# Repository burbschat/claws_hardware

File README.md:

# Simple SiPM/plastic scintillator based beam loss monitors
## Introduction
This repository contains the hardware design for a kind of SiPM/plastic
scintillator based beam loss monitor.
The design is based on and borrows the name (*CLAWS*) from an earlier design
employed during commissioning of the SuperKEKB collider.
A related thesis can be found [here](https://mediatum.ub.tum.de/1624845).
CLAWS was supposed to be a abbreviation for some longer name but it surely
wasn't a very elegant one, neither can I seem to remember it. Anyhow, as a
short name is quite practical, we kept on calling the system *CLAWS*.

The sensors later have been re-purposed to detect beam loss and trigger a beam
abort if there is too much of it. This application does not require very
precise sensors. Further, opposed to the original design, now a larger dynamic
range was desirable. To also allow for measurement of beam backgrounds
which occur for longer than a few microseconds, DC coupled analog electronics
are required.
The design published here was created to implement the required changes
outlined above and create a system better suited to the current application at
the SuperKEKB collider.

## Disclaimer
The circuits here have been designed by an at the time undergrad student (me)
who had no real experience in electronics or electronics CAD. I am sure there
are many aspects that I would do differently now, be it related to the circuit
itself or how it is described in KiCad.
I am however of course open for suggestions to improve the design (although I
cannot guarantee I will find the time to implement them myself).

## Overview
There are two parts to the detector system: The detectors, which are to be
placed where the beam background is expected to occur and the receiver board,
which should be placed near the digitizer, which is usually positioned outside
the radiation controlled area of the accelerator complex.

The following is an illustration of the use case at SuperKEKB (use for beam
abort), also illustrating the detector structure.
We employ a special trigger to reject short background spikes. The analog
signal however can be used in any other conceivable way depending on the exact
application.

### Detector Board
The detector (sometimes also referred to as the sensor) is based on a plastic
scintillator (BC-408 or similar material), light from which is detected using a
Hamamatsu SiPM (or MPPC). The SiPM is located in a small dimple in the bottom
of the scintillator. The scintillator is wrapped in an appropriately sized
reflective film (M3 DF2000MA or similar) to make sure as much as possible light
reaches the SiPM. This is the same as what was used with the earlier versions
of CLAWS and can be traced back to what is described in [this paper](https://arxiv.org/abs/1512.05900).
The wrapped scintillator is fixed to the PCB using black aluminium tape, which
also serves to shut out any light from the environment, which would overwhelm
(and potentially damage) the SiPM.

The signal obtained from the SiPM is turned into a differential signal using
the LMH6553 fully differential amplifier. The gain of this amplifier may be set
by choosing appropriate resistor values in the feedback loops of the circuit.
This amplifier then drives a differential pair in an ordinary Ethernet cable.
However, generally only CAT6A or CAT7 cables are used, as they usually provide
superior shielding, which even though a differential pair is used, appeared to
significantly lower the noise introduced by the cable.

The required voltages to drive the amplifier circuit as well as the SiPM bias
voltage are obtained from the same Ethernet cable. The amplifier here is
configured with a single 10V power supply. The voltage in the cable should be
slightly above 10V, as it is regulated by a LDO regulator on the detector
board.
10V is the maximum supply voltage supported by the LMH6553 and is chosen to
maximize the dynamic range at the amplifier output (which depends on the supply
voltage).

One twisted pair in the cable remains unused for now.

### Receiver Board
The differential signal provided by the detector board is received and properly
terminated by the receiver board. It contains a circuit using the same LMH6553
fully differential amplifier, which provides further amplification of the
received signal, as well as the option to convert it to a single ended signal.
Both inverted and non-inverted signals are supported. The not used side must be
terminated using a 50Ohm resistor (which can however also be mounted directly
on the board while leaving the corresponding output connector unpopulated).
There also is the option to further use both outputs at the same time to obtain
a differential signal.

The receiver amplifier circuit is, opposed to the one on the detector board,
arranged in a symmetric configuration. This is done to avoid a large DC bias at
the output, which poses no problem for in case of the detector board, as it is
removed by the receiver amplification circuit. The symmetric configuration
necessitates +5V and -5V supplies (for both of which there are LDO regulators
on the board).

Presumably due some unavoidable variations in the used components (resistance
values etc.), the circuit is never perfectly symmetric and thus a small DC bias
remains. The same bias appears at both outputs (inverted and non-inverted).
To compensate this, the common mode output voltage control pin of the LMH6553
is used, which is accessible through a potentiometer on the board.
As the bias is present at both outputs, one can only ever tune the circuit to
have one of them centered perfectly around zero. This however should pose no
significant problem, as in most use cases one probably only uses one of the two
outputs, or uses both to get a differential signal, for which a small DC bias
does not matter.

The Receiver board further also distributes the voltages required by the
detector boards. These voltages as well as those needed by the receiver board
itself are supplied externally through connectors on the side of the board.
There further is the option to daisy-chain multiple receiver boards and share
the supply voltages between them. Which voltage should be connected to what is
to some degree configurable using a set of jumper pins. As regulators are used
for all but the SiPM bias voltage, the low voltages provided can be chosen
rather freely, as long as they fall within the ranges supported input of the
LDO regulators. However, testing showed that if they are on the high side, the
LDOs get rather hot. Whether this is still within the supported temperature
range was not (yet) verified.

There is also an option to use the positive voltage (before the LDO) for the
receiver board amplifier as the positive voltage for the detector board
amplifier. This turned out to be the most convenient configuration as it allows 
the setup to be powered off a +/-12V double rail supply (next to a supply for
the SiPM bias voltage).

To share voltages between receiver boards, a 10-pin ribbon cable is used. The
boards may be arranged in a stacked configuration, in case of which the
connector on the bottom must be installed and used, or a flat configuration
with a single long ribbon cable with multiple connectors.

A example for the stacked configuration is shown below. There is theoretically
also the option to add further boards of the same form factor which for example
may contain a high voltage power supply to provide the SiPM bias voltage, or
DC/DC converters to provide the other supply voltages. A mockup is shown in the
figure below.

### SiPM Bias Voltage Supply
To avoid having to prepare a adjustable power supply supporting up to ~60V for
every setup, it was attempted to design a simple circuit based on the LT3571
75V DC/DC Converter for APD Bias.
The design appears to function alright, but does not provide a very flat voltage.
This to some extend is reflected in the signal form the SiPM. However, for the
application at SuperKEKB, the signal does not have to be very precise and the
introduced noise can be tolerated.

The board also does indeed emit some EMI, so care must be taken on where to
position it. There likely are possibilities to improve this design. I am open
for suggestions.

The board can be run off the same +12V as used as an input to the receiver
board. There is the option to use a DAC in combination with a microcontroller
to set the voltages and possibly read them back. I did not yet get around to
prepare a proper firmware for that. One can also simply adjust the voltage 
using a potentiometer.

There are four channels on one board, just because four of them appeared to
fit. One can just not populate the unused ones, if less than four are required.
The board does not support the same interconnect headers as the receiver boards.
This is because it mainly was designed to see if the circuit does work/is
usable at all. One could create a new version with only one channel featuring
the interconnect header.

## KiCad
The design is entirely drawn in KiCad. I like to use the newest version. The
files in this repository are for version 9.

## Libraries
There is are custom symbol and footprint library containing all the parts not
present in the standard KiCad libraries. The provided 3D models are managed
with git LFS.

## Simulation
Some of the symbols reference SPICE models in the `${KIPRJMOD}/../lib/spice_models/` directory.
Those are not present in this repository as I am probably not permitted to distribute them.
If simulation is required, please acquire the models directly from the manufacturers.

## KiBot
KiBot can be used to automate creation of gerber files, export circuit diagrams
and assembly documents or similar. The included configs are those which I used
when producing the boards at use for the SuperKEKB abort system. Adjust to taste.

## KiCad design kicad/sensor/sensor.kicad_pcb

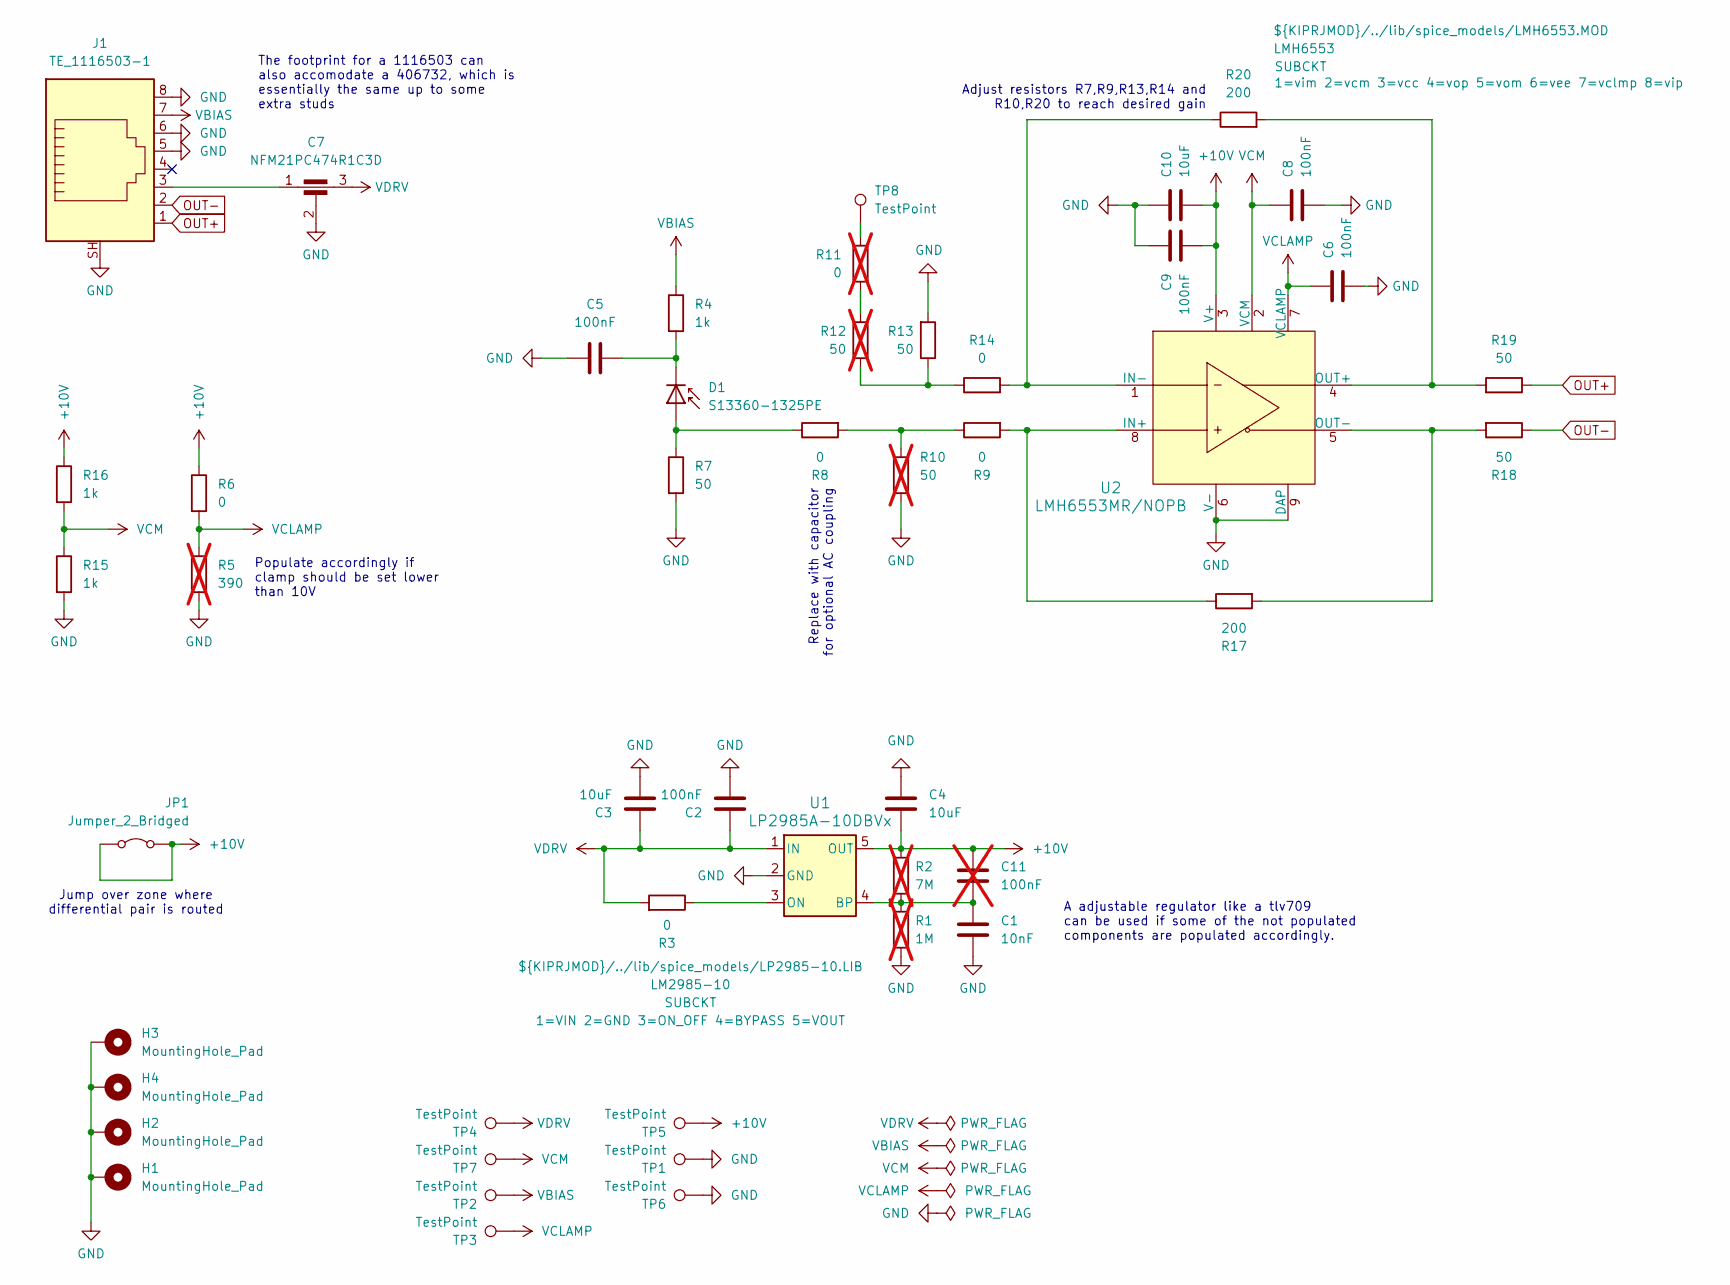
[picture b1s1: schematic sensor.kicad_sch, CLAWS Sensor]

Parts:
C1: 10nF; C_0603_1608Metric; Part Number GRM188R72A103KA01D
C2, C5, C6, C8, C9: 100nF; C_0603_1608Metric; Part Number GRM188R72A104KA35D
C3, C4, C10: 10uF; C_0603_1608Metric; Part Number GRM188R61E106KA73D
C7: NFM21PC474R1C3D; NFM21PC225B0J3D_MUR; Part Number NFM21PC474R1C3D
C11: 100nF; C_0603_1608Metric; Part Number GRM188R72A104KA35D; not fitted
D1: S13360-1325PE; Hamamatsu_Sxxx60-13xxXX_hand_solder; Part Number S13360-1325PE
H1, H2, H3, H4: MountingHole_Pad; MountingHole_3.2mm_M3_ISO7380_Pad_TopBottom
J1: TE_1116503-1; TE_1116503; Part Number TE_1116503-1
JP1: Jumper_2_Bridged; R_2512_6332Metric; Part Number ERJ-U1T0R00U
R1: 1M; R_0603_1608Metric; not fitted
R2: 7M; R_0603_1608Metric; not fitted
R3, R6, R8, R9, R14: 0; R_0603_1608Metric; Part Number ERJ-3GEY0R00V
R4, R15, R16: 1k; R_0603_1608Metric; Part Number ERJ-3EKF1001V
R5: 390; R_0603_1608Metric; not fitted
R7, R13, R18, R19: 50; R_0603_1608Metric; Part Number ERJ-3EKF49R9V
R10, R12: 50; R_0603_1608Metric; Part Number ERJ-3EKF49R9V; not fitted
R11: 0; R_0603_1608Metric; Part Number ERJ-3GEY0R00V; not fitted
R17, R20: 200; R_0603_1608Metric; Part Number ERJ-3GEYJ201V
TP1, TP2, TP3, TP4, TP5, TP6, TP7, TP8: TestPoint; TestPoint_THTPad_D1.5mm_Drill0.7mm
U1: LP2985A-10DBVx; SOT-23-5_DBV_TEX; Part Number LP2985A-10DBVR
U2: LMH6553MR/NOPB; MRA08B; Part Number LMH6553MRE/NOPB

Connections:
+10V: C4.1, C9.1, C10.1, C11.2, JP1.1 (A), JP1.2 (B), R2.1, R6.1, R16.1, TP5.1, U1.5 (OUT), U2.3 (V+)
GND: C1.1, C2.1, C3.1, C4.2, C5.1, C6.1, C7.2, C8.1, C9.2, C10.2, H1.1, H2.1, H3.1, H4.1, J1.5, J1.6, J1.8, J1.SH, R1.2, R5.2, R7.2, R10.2, R13.2, R15.2, TP1.1, TP6.1, U1.2 (GND), U2.6 (V-), U2.9 (DAP)
unnamed: C7.1, J1.3
unnamed: D1.3 (A), R7.1, R8.1
unnamed: C5.2, D1.2 (K), R4.2
unnamed: R8.2, R9.1, R10.1
unnamed: R11.1, TP8.1
unnamed: R11.2, R12.2
unnamed: R12.1, R13.1, R14.1
unnamed: C1.2, C11.1, R1.1, R2.2, U1.4 (BP)
unnamed: R3.1, U1.3 (ON)
unnamed: R9.2, R17.1, U2.8 (IN+)
unnamed: R14.2, R20.1, U2.1 (IN-)
unnamed: R19.2, R20.2, U2.4 (OUT+)
unnamed: R17.2, R18.2, U2.5 (OUT-)
OUT+: J1.1, R19.1
OUT-: J1.2, R18.1
VBIAS: J1.7, R4.1, TP2.1
VCLAMP: C6.2, R5.1, R6.2, TP3.1, U2.7 (VCLAMP)
VCM: C8.2, R15.1, R16.2, TP7.1, U2.2 (VCM)
VDRV: C2.2, C3.2, C7.3, R3.2, TP4.1, U1.1 (IN)

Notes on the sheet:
Adjust resistors R7,R9,R13,R14 and R10,R20 to reach desired gain
Replace with capacitor for optional AC coupling
The footprint for a 1116503 can also accomodate a 406732, which is essentially the same up to some extra studs
A adjustable regulator like a tlv709 can be used if some of the not populated components are populated accordingly.
Populate accordingly if clamp should be set lower than 10V
Jump over zone where differential pair is routed

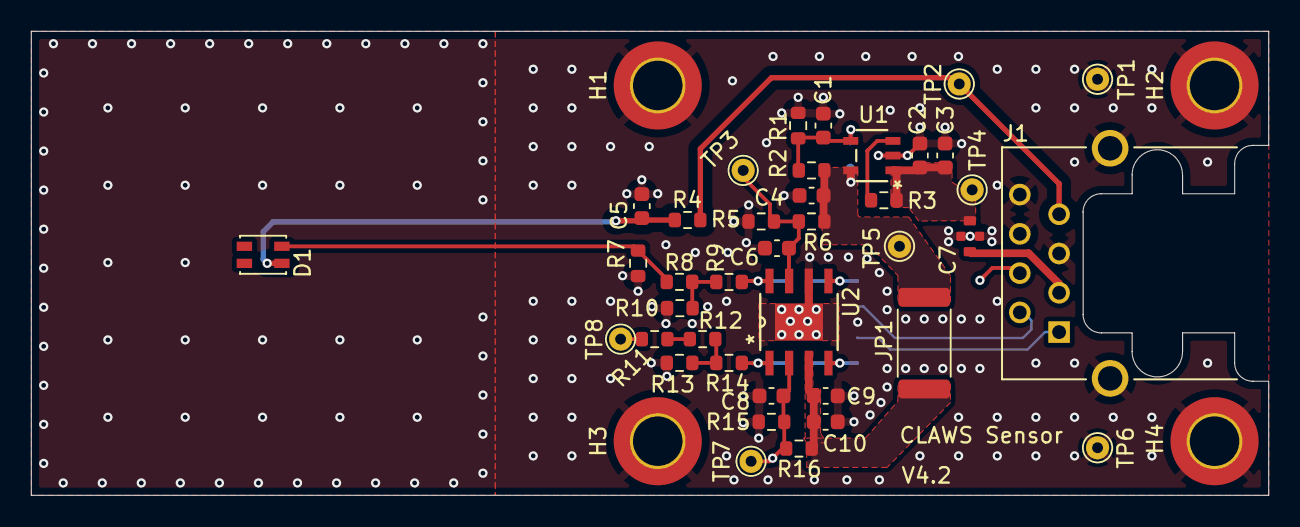
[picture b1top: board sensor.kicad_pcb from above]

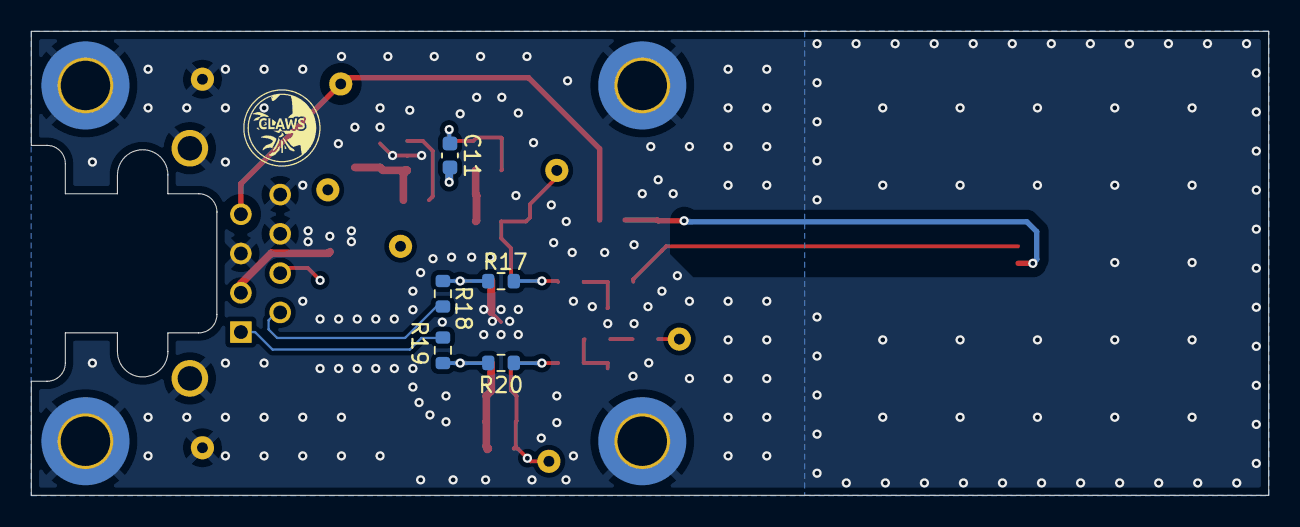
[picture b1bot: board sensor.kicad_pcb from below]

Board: 2 copper layers, 80.0 x 30.0 mm, 48 parts (5 on the bottom side), 21 nets.

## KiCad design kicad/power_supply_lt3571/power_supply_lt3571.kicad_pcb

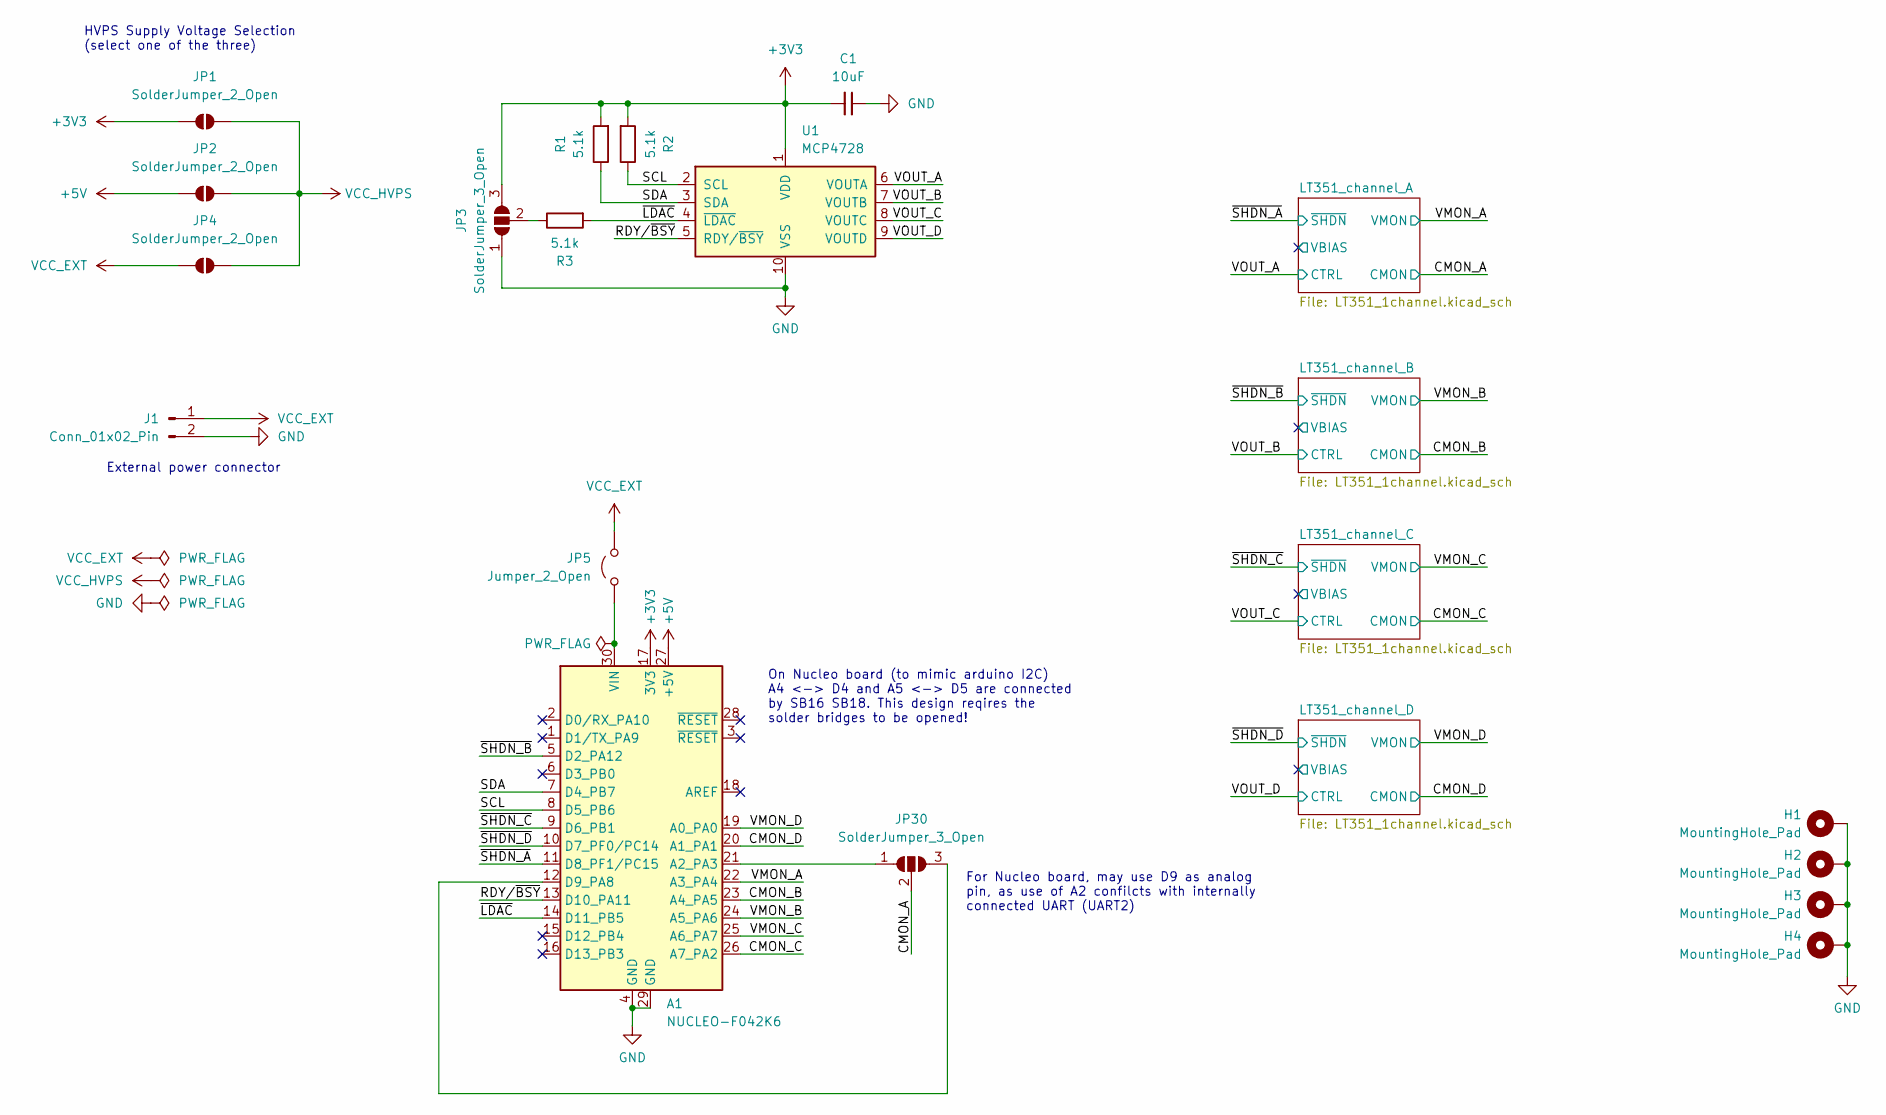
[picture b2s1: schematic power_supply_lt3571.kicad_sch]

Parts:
A1: NUCLEO-F042K6; NUCLEO_NANO_Hybrid
C1: 10uF; C_0603_1608Metric
H1, H2, H3, H4: MountingHole_Pad; MountingHole_3.2mm_M3_Pad_Via
J1: Conn_01x02_Pin; PhoenixContact_MCV_1,5_2-G-3.81_1x02_P3.81mm_Vertical
JP1, JP2, JP4: SolderJumper_2_Open; SolderJumper-2_P1.3mm_Open_TrianglePad1.0x1.5mm
JP3, JP30: SolderJumper_3_Open; SolderJumper-3_P2.0mm_Open_TrianglePad1.0x1.5mm_NumberLabels
JP5: Jumper_2_Open; PinHeader_1x02_P2.54mm_Vertical
R1, R2, R3: 5.1k; R_0603_1608Metric
U1: MCP4728; MSOP-10_3x3mm_P0.5mm

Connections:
+3V3: A1.17 (3V3), C1.2, JP1.1 (A), JP3.3 (B), R1.2, R2.2, U1.1 (VDD)
+5V: A1.27 (+5V), JP2.1 (A)
/CMON_A: JP30.2 (C); also elsewhere on the board
/CMON_B: A1.23 (A4_PA5); also elsewhere on the board
/CMON_C: A1.26 (A7_PA2); also elsewhere on the board
/CMON_D: A1.20 (A1_PA1); also elsewhere on the board
/RDY/~BSY: A1.13 (D10_PA11), U1.5 (RDY/~BSY)
/SCL: A1.8 (D5_PB6), R2.1, U1.2 (SCL)
/SDA: A1.7 (D4_PB7), R1.1, U1.3 (SDA)
/VMON_A: A1.22 (A3_PA4); also elsewhere on the board
/VMON_B: A1.24 (A5_PA6); also elsewhere on the board
/VMON_C: A1.25 (A6_PA7); also elsewhere on the board
/VMON_D: A1.19 (A0_PA0); also elsewhere on the board
/VOUT_A: U1.6 (VOUTA); also elsewhere on the board
/VOUT_B: U1.7 (VOUTB); also elsewhere on the board
/VOUT_C: U1.8 (VOUTC); also elsewhere on the board
/VOUT_D: U1.9 (VOUTD); also elsewhere on the board
/~LDAC: A1.14 (D11_PB5), R3.2, U1.4 (~LDAC)
/~SHDN_A: A1.11 (D8_PF1/PC15); also elsewhere on the board
/~SHDN_B: A1.5 (D2_PA12); also elsewhere on the board
/~SHDN_C: A1.9 (D6_PB1); also elsewhere on the board
/~SHDN_D: A1.10 (D7_PF0/PC14); also elsewhere on the board
GND: A1.4 (GND), A1.29 (GND), C1.1, H1.1, H2.1, H3.1, H4.1, J1.2, JP3.1 (A), U1.10 (VSS); also elsewhere on the board
unnamed: A1.21 (A2_PA3), JP30.1 (A)
unnamed: A1.12 (D9_PA8), JP30.3 (B)
unnamed: A1.30 (VIN), JP5.1 (A)
unnamed: JP3.2 (C), R3.1
VCC_EXT: J1.1, JP4.1 (A), JP5.2 (B)
VCC_HVPS: JP1.2 (B), JP2.2 (B), JP4.2 (B); also elsewhere on the board

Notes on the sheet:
On Nucleo board (to mimic arduino I2C) A4 <-> D4 and A5 <-> D5 are connected by SB16 SB18. This design reqires the solder bridges to be opened!
External power connector
HVPS Supply Voltage Selection (select one of the three)
For Nucleo board, may use D9 as analog pin, as use of A2 confilcts with internally connected UART (UART2)

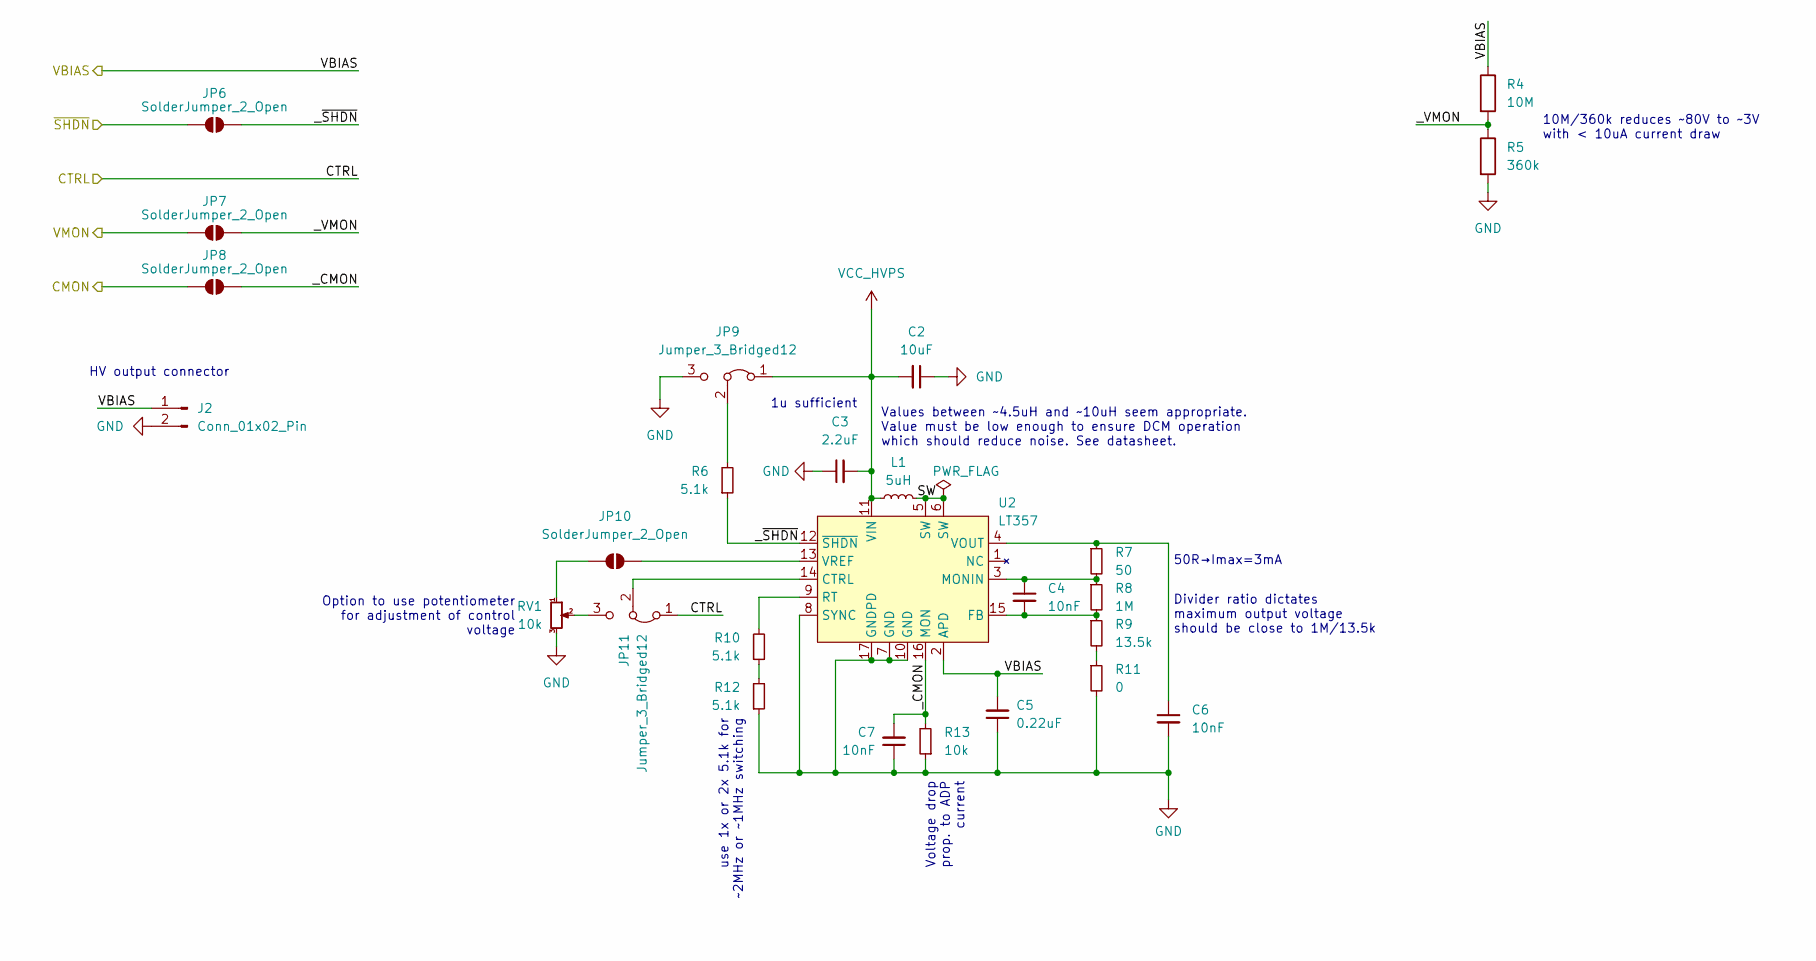
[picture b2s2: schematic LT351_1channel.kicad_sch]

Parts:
C2: 10uF; C_0603_1608Metric
C3: 2.2uF; C_0603_1608Metric
C4, C6, C7: 10nF; C_0603_1608Metric
C5: 0.22uF; C_1206_3216Metric
J2: Conn_01x02_Pin; PhoenixContact_MC_1,5_2-G-3.81_1x02_P3.81mm_Horizontal
JP6, JP7, JP8, JP10: SolderJumper_2_Open; SolderJumper-2_P1.3mm_Open_TrianglePad1.0x1.5mm
JP9, JP11: Jumper_3_Bridged12; PinHeader_1x03_P2.54mm_Vertical
L1: 5uH; L_1210_3225Metric
R4: 10M; R_0603_1608Metric
R5: 360k; R_0603_1608Metric
R6, R10, R12: 5.1k; R_0603_1608Metric
R7: 50; R_0603_1608Metric
R8: 1M; R_0603_1608Metric
R9: 13.5k; R_0603_1608Metric
R11: 0; R_0603_1608Metric
R13: 10k; R_0603_1608Metric
RV1: 10k; Potentiometer_Bourns_3296X_Horizontal
U2: LT357; QFN-16-1EP_3x3mm_P0.5mm_EP1.45x1.45mm_ThermalVias

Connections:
/CMON_A: JP8.1 (A); also elsewhere on the board
/LT351_channel_A/SW: L1.2, U2.5 (SW), U2.6 (SW)
/LT351_channel_A/VBIAS: C5.2, J2.1, R4.1, U2.2 (APD)
/LT351_channel_A/_CMON: C7.2, JP8.2 (B), R13.2, U2.16 (MON)
/LT351_channel_A/_VMON: JP7.2 (B), R4.2, R5.1
/LT351_channel_A/_~SHDN: JP6.2 (B), R6.1, U2.12 (~SHDN)
/VMON_A: JP7.1 (A); also elsewhere on the board
/VOUT_A: JP11.1 (A); also elsewhere on the board
/~SHDN_A: JP6.1 (A); also elsewhere on the board
GND: C2.1, C3.1, C5.1, C6.2, C7.1, J2.2, JP9.3 (B), R5.2, R11.2, R12.1, R13.1, RV1.3, U2.7 (GND), U2.8 (SYNC), U2.10 (GND), U2.17 (GNDPD); also elsewhere on the board
unnamed: JP9.2 (C), R6.2
unnamed: JP10.1 (A), RV1.1
unnamed: JP10.2 (B), U2.13 (VREF)
unnamed: JP11.3 (B), RV1.2
unnamed: JP11.2 (C), U2.14 (CTRL)
unnamed: R10.1, R12.2
unnamed: R9.2, R11.1
unnamed: C4.2, R8.2, R9.1, U2.15 (FB)
unnamed: C4.1, R7.2, R8.1, U2.3 (MONIN)
unnamed: R10.2, U2.9 (RT)
unnamed: C6.1, R7.1, U2.4 (VOUT)
VCC_HVPS: C2.2, C3.2, JP9.1 (A), L1.1, U2.11 (VIN); also elsewhere on the board

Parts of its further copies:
C8, C14, C20: 10uF; C_0603_1608Metric
C9, C15, C21: 2.2uF; C_0603_1608Metric
C10, C12, C13, C16, C18, C19, C22, C24, C25: 10nF; C_0603_1608Metric
C11, C17, C23: 0.22uF; C_1206_3216Metric
J3, J4, J5: Conn_01x02_Pin; PhoenixContact_MC_1,5_2-G-3.81_1x02_P3.81mm_Horizontal
JP12, JP13, JP14, JP16, JP18, JP19, JP20, JP22, JP24, JP25, JP26, JP28: SolderJumper_2_Open; SolderJumper-2_P1.3mm_Open_TrianglePad1.0x1.5mm
JP15, JP17, JP21, JP23, JP27, JP29: Jumper_3_Bridged12; PinHeader_1x03_P2.54mm_Vertical
L2, L3, L4: 5uH; L_1210_3225Metric
R14, R24, R34: 10M; R_0603_1608Metric
R15, R25, R35: 360k; R_0603_1608Metric
R16, R20, R22, R26, R30, R32, R36, R40, R42: 5.1k; R_0603_1608Metric
R17, R27, R37: 50; R_0603_1608Metric
R18, R28, R38: 1M; R_0603_1608Metric
R19, R29, R39: 13.5k; R_0603_1608Metric
R21, R31, R41: 0; R_0603_1608Metric
R23, R33, R43: 10k; R_0603_1608Metric
RV2, RV3, RV4: 10k; Potentiometer_Bourns_3296X_Horizontal
U3, U4, U5: LT357; QFN-16-1EP_3x3mm_P0.5mm_EP1.45x1.45mm_ThermalVias

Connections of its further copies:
/CMON_B: JP14.1 (A); also elsewhere on the board
/CMON_C: JP20.1 (A); also elsewhere on the board
/CMON_D: JP26.1 (A); also elsewhere on the board
/LT351_channel_B/SW: L2.2, U3.5 (SW), U3.6 (SW)
/LT351_channel_B/VBIAS: C11.2, J3.1, R14.1, U3.2 (APD)
/LT351_channel_B/_CMON: C13.2, JP14.2 (B), R23.2, U3.16 (MON)
/LT351_channel_B/_VMON: JP13.2 (B), R14.2, R15.1
/LT351_channel_B/_~SHDN: JP12.2 (B), R16.1, U3.12 (~SHDN)
/LT351_channel_C/SW: L3.2, U4.5 (SW), U4.6 (SW)
/LT351_channel_C/VBIAS: C17.2, J4.1, R24.1, U4.2 (APD)
/LT351_channel_C/_CMON: C19.2, JP20.2 (B), R33.2, U4.16 (MON)
/LT351_channel_C/_VMON: JP19.2 (B), R24.2, R25.1
/LT351_channel_C/_~SHDN: JP18.2 (B), R26.1, U4.12 (~SHDN)
/LT351_channel_D/SW: L4.2, U5.5 (SW), U5.6 (SW)
/LT351_channel_D/VBIAS: C23.2, J5.1, R34.1, U5.2 (APD)
/LT351_channel_D/_CMON: C25.2, JP26.2 (B), R43.2, U5.16 (MON)
/LT351_channel_D/_VMON: JP25.2 (B), R34.2, R35.1
/LT351_channel_D/_~SHDN: JP24.2 (B), R36.1, U5.12 (~SHDN)
/VMON_B: JP13.1 (A); also elsewhere on the board
/VMON_C: JP19.1 (A); also elsewhere on the board
/VMON_D: JP25.1 (A); also elsewhere on the board
/VOUT_B: JP17.1 (A); also elsewhere on the board
/VOUT_C: JP23.1 (A); also elsewhere on the board
/VOUT_D: JP29.1 (A); also elsewhere on the board
/~SHDN_B: JP12.1 (A); also elsewhere on the board
/~SHDN_C: JP18.1 (A); also elsewhere on the board
/~SHDN_D: JP24.1 (A); also elsewhere on the board
GND: C8.1, C9.1, C11.1, C12.2, C13.1, C14.1, C15.1, C17.1, C18.2, C19.1, C20.1, C21.1, C23.1, C24.2, C25.1, J3.2, J4.2, J5.2, JP15.3 (B), JP21.3 (B), JP27.3 (B), R15.2, R21.2, R22.1, R23.1, R25.2, R31.2, R32.1, R33.1, R35.2, R41.2, R42.1, R43.1, RV2.3, RV3.3, RV4.3, U3.7 (GND), U3.8 (SYNC), U3.10 (GND), U3.17 (GNDPD), U4.7 (GND), U4.8 (SYNC), U4.10 (GND), U4.17 (GNDPD), U5.7 (GND), U5.8 (SYNC), U5.10 (GND), U5.17 (GNDPD); also elsewhere on the board
unnamed: JP15.2 (C), R16.2
unnamed: JP16.1 (A), RV2.1
unnamed: JP16.2 (B), U3.13 (VREF)
unnamed: JP17.3 (B), RV2.2
unnamed: JP17.2 (C), U3.14 (CTRL)
unnamed: JP21.2 (C), R26.2
unnamed: JP22.1 (A), RV3.1
unnamed: JP22.2 (B), U4.13 (VREF)
unnamed: JP23.3 (B), RV3.2
unnamed: JP23.2 (C), U4.14 (CTRL)
unnamed: JP27.2 (C), R36.2
unnamed: JP28.1 (A), RV4.1
unnamed: JP28.2 (B), U5.13 (VREF)
unnamed: JP29.3 (B), RV4.2
unnamed: JP29.2 (C), U5.14 (CTRL)
unnamed: R19.2, R21.1
unnamed: R20.1, R22.2
unnamed: R29.2, R31.1
unnamed: R30.1, R32.2
unnamed: R39.2, R41.1
unnamed: R40.1, R42.2
unnamed: C10.2, R18.2, R19.1, U3.15 (FB)
unnamed: C10.1, R17.2, R18.1, U3.3 (MONIN)
unnamed: R20.2, U3.9 (RT)
unnamed: C12.1, R17.1, U3.4 (VOUT)
unnamed: C16.2, R28.2, R29.1, U4.15 (FB)
unnamed: C16.1, R27.2, R28.1, U4.3 (MONIN)
unnamed: R30.2, U4.9 (RT)
unnamed: C18.1, R27.1, U4.4 (VOUT)
unnamed: C22.2, R38.2, R39.1, U5.15 (FB)
unnamed: C22.1, R37.2, R38.1, U5.3 (MONIN)
unnamed: R40.2, U5.9 (RT)
unnamed: C24.1, R37.1, U5.4 (VOUT)
VCC_HVPS: C8.2, C9.2, C14.2, C15.2, C20.2, C21.2, JP15.1 (A), JP21.1 (A), JP27.1 (A), L2.1, L3.1, L4.1, U3.11 (VIN), U4.11 (VIN), U5.11 (VIN); also elsewhere on the board

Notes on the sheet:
HV output connector
50R→Imax=3mA
use 1x or 2x 5.1k for ~2MHz or ~1MHz switching
10M/360k reduces ~80V to ~3V with < 10uA current draw
Values between ~4.5uH and ~10uH seem appropriate. Value must be low enough to ensure DCM operation which should reduce noise. See datasheet.
1u sufficient
Divider ratio dictates maximum output voltage should be close to 1M/13.5k
Option to use potentiometer for adjustment of control voltage
Voltage drop prop. to ADP current

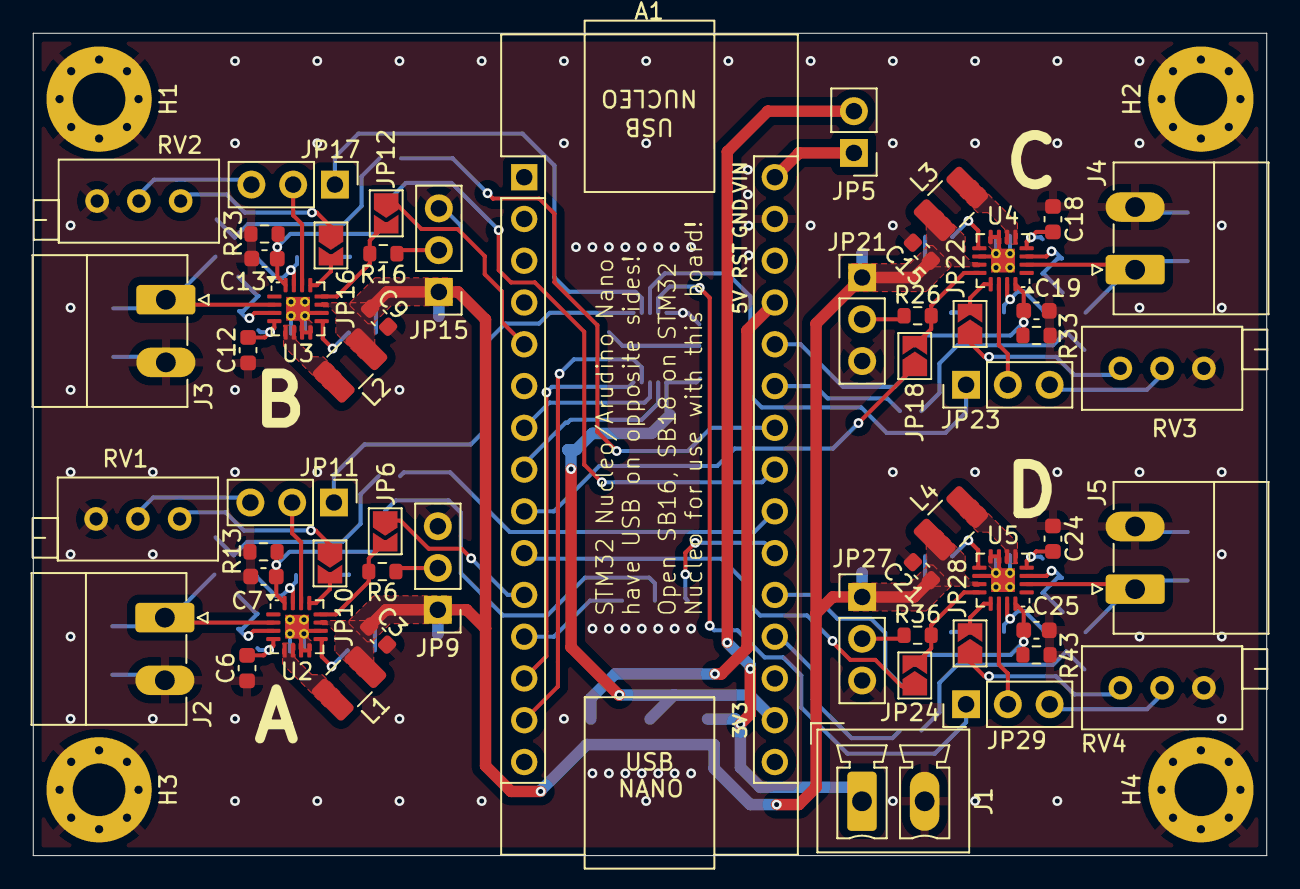
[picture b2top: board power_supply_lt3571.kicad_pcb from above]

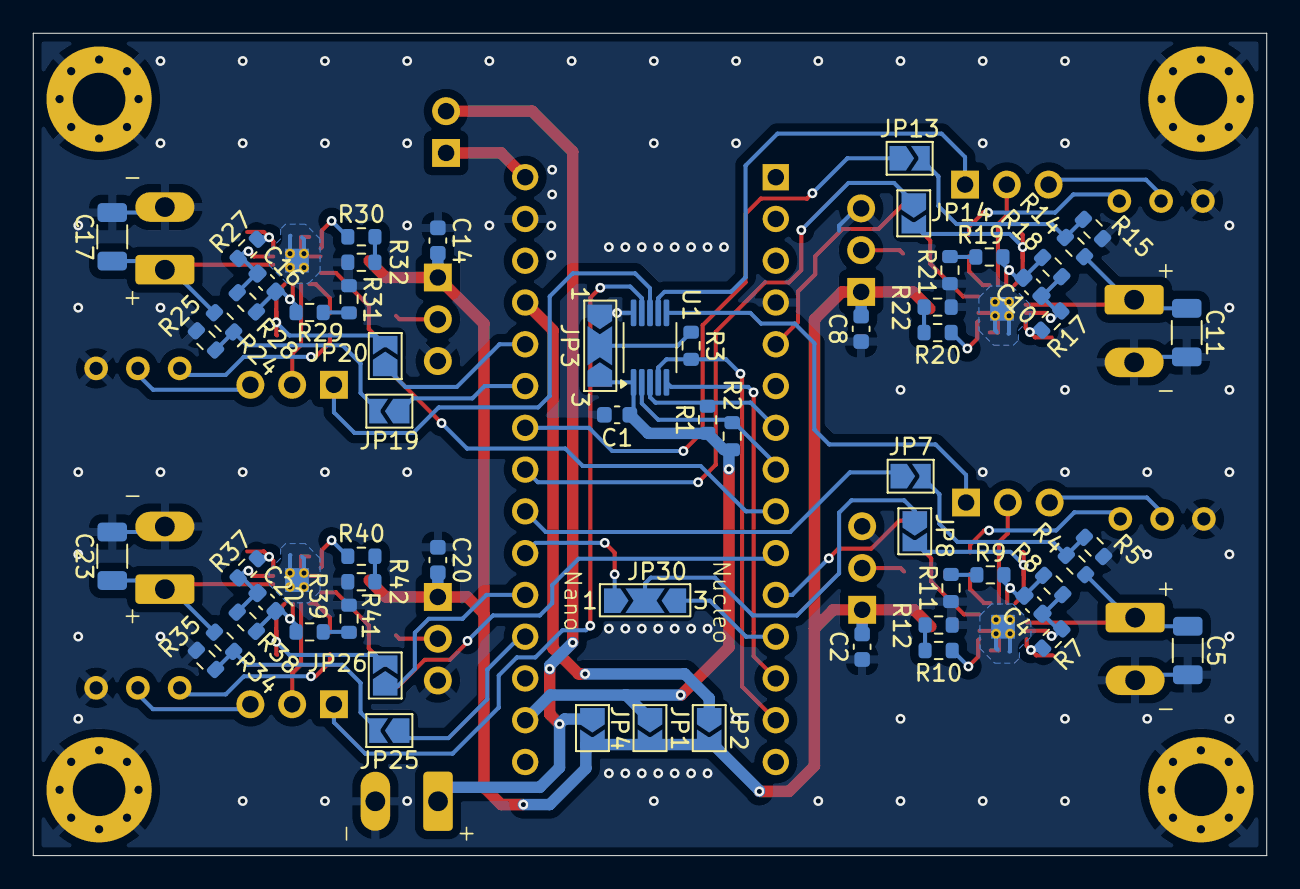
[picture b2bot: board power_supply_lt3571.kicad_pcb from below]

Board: 2 copper layers, 75.0 x 50.0 mm, 121 parts (62 on the bottom side), 93 nets.
